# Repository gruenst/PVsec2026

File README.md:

# Open Source Hardware for Mobile String Power Acquisition of Solar Parks
Circuitpython and C++ based measurement system for Photovoltaic Installations. Up to 10 current clamps can be integrated, additional voltage, current and module temperature acquisition.

## Purpose
 * Open-source enhancements of publicly available hardware resources with LoRa radio for long range sensor data acquisition capability (no mesh network).
 * Complete system for measuring solar parks with flawed or without string monitoring
 * Versatile alternative to IV curve acquisition systems specifically for systems without single string accessibility - adapt to your own liking.

## Usage
 * Plug device in, opens up as USB stick (circuitpython)
 * Open .html file in Web Serial API compatible browser (Chrome, Edge, Opera; see https://developer.mozilla.org/en-US/docs/Web/API/Serial)
 * Use browser as GUI, connect to device and send/receive commands to/from device via serial interface
 * commands will be forwarded via LoRa RFM98W radio chip to remote device
 
## Content
 - Descriptions:    Short descriptions of each system with pictures 
 - PCBs, BOM:       EAGLE Cad PCB files, list of components
 - Housing:         3D STP files for 3D printing
 - Circuit Python:  Circuitpython .uf2, device code
 - GUI:             code.py for device, .html code with .js elements for GUI control, Arduino C++ code, web Serial or WLAN websocket control
 - bootloader:      Atmel SAMD bootloader for JLink
[https://learn.adafruit.com/how-to-program-samd-bootloaders](https://learn.adafruit.com/how-to-program-samd-bootloaders)

## Manual
 - Make PCB, solder components
 - flash bootloader using .bin file, e.g. via JLink, see https://learn.adafruit.com/how-to-program-samd-bootloaders
 - mount device via usb, put into bootloader mode, upload circuitpython .uf2 file
 - copy circuitpython8 lib elements to /lib directory on device
 - put code.py to device
 - upload .html file to device, adjust accordingly
 enjoy!
 
[Grn.Solar](https://www.grn.solar)
 
 Big shoutouts to [Adafruit](https://www.adafruit.com "Adafruit rocks") and Flaticon.

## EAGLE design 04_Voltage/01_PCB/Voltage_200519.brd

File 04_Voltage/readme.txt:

Lazy build for embedding a Phoenix Contact DC voltage level shifter (SCK-M-U-1500V) into a 3D printed case.
These components should be on the board:
 - 24V supply for the Phoenix Contact, power by 5V:  Murata NME0524DC
 - Adafruit ADS1115 breakout board
 - Adafruit PowerBoost 1000 Charger
 - Adafruit ItsyBitys M4 express
 
Embedding everything on a single PCB would be beneficial, but using an industry standard for 1500V string voltages seems reasonable.

DC connection via panel mount plugs (banana or solar connectors).
Power switch, with LED.
USB and SMA antenna plugs recommended.

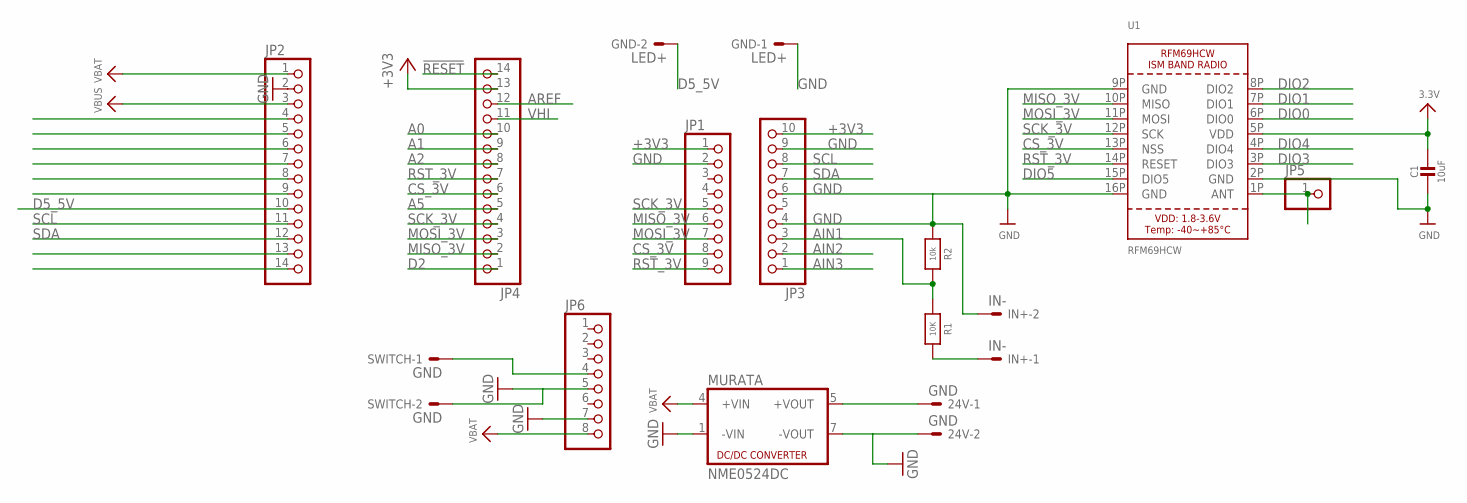
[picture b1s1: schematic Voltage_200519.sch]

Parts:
24V: GND; 332-02
C1: 10uF; 0805-NO@1
GND: LED+; 332-02
IN+: IN-; 332-02
JP1: HEADER-1X970MIL; 1X09_ROUND_70
JP2, JP4: HEADER-1X14; 1X14_ROUND70
JP3: HEADER-1X1070MIL; 1X10_ROUND70
JP5: HEADER-1X1ROUND; 1X01_ROUND
JP6: HEADER-1X8ROUND; 1X08_ROUND
MURATA: NME0524DC; 8DIL-4
R1: 10K; 0805-NO
R2: 10k; 0805-NO
SWITCH: GND; 332-02
U1: RFM69HCW; RFMHCW_SMT

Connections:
!RESET: JP4.14
+3V3: C1.1, JP1.1, JP3.10, JP4.13, U1.5P (VDD)
A0: JP4.10
A1: JP4.9
A2: JP4.8
A5: JP4.5
AIN1: JP3.3, R1.1, R2.2
AIN2: JP3.2
AIN3: JP3.1
AREF: JP4.12
CS_3V: JP1.8, JP4.6, U1.13P (NSS)
D2: JP4.1
D5_5V: GND.2, JP2.10
D7: JP2.9
D9: JP2.8
D10: JP2.7
D11: JP2.6
D12: JP2.5
D13: JP2.4
DIO0: U1.6P (DIO0)
DIO1: U1.7P (DIO1)
DIO2: U1.8P (DIO2)
DIO3: U1.3P (DIO3)
DIO4: U1.4P (DIO4)
DIO5: U1.15P (DIO5)
GND: 24V.2, C1.2, GND.1, IN+.2, JP1.2, JP2.2, JP3.4, JP3.6, JP3.9, JP6.5, JP6.7, MURATA.1 (-VIN), MURATA.7 (-VOUT), R2.1, SWITCH.2, U1.2P (GND), U1.9P (GND), U1.16P (GND)
MISO_3V: JP1.6, JP4.2, U1.10P (MISO)
MOSI_3V: JP1.7, JP4.3, U1.11P (MOSI)
unnamed: JP5.1, U1.1P (ANT)
unnamed: JP6.4, SWITCH.1
unnamed: IN+.1, R1.2
unnamed: 24V.1, MURATA.5 (+VOUT)
RST_3V: JP1.9, JP4.7, U1.14P (RESET)
RX_D0: JP2.14
SCK_3V: JP1.5, JP4.4, U1.12P (SCK)
SCL: JP2.11, JP3.8
SDA: JP2.12, JP3.7
TX_D1: JP2.13
VBAT: JP2.1, JP6.8, MURATA.4 (+VIN)
VBUS: JP2.3
VHI: JP4.11

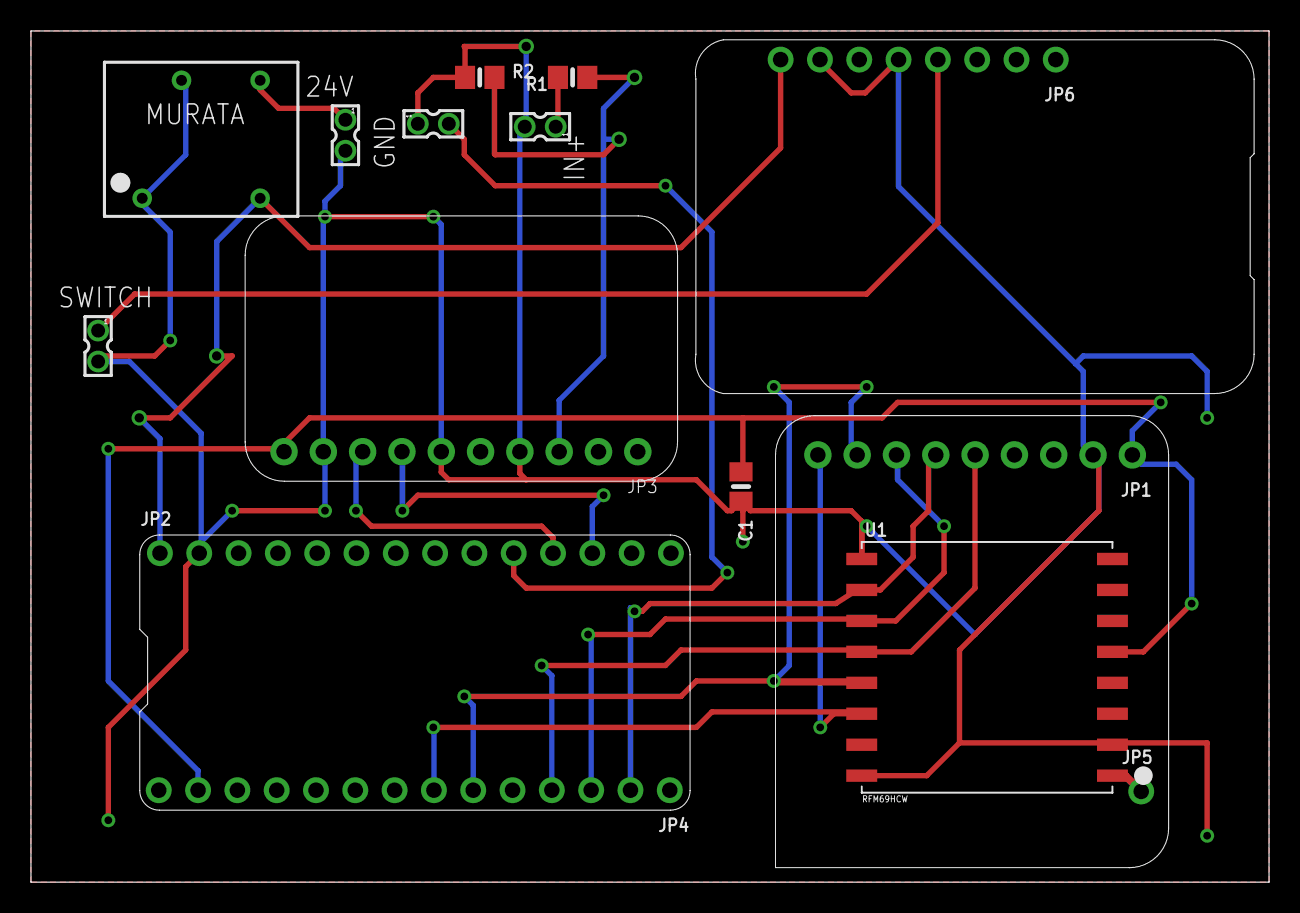
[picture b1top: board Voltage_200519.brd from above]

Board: 2 copper layers, 80.0 x 55.0 mm, 15 parts (0 on the bottom side), 16 nets.

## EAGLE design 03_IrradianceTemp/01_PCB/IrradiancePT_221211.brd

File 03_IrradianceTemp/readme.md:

# irradiance sensor with module temperature acquisition

Modification/hack of standard M&T irradiance sensors with an own-made PCB, and battery for independent operation.
As the current clamps, this is base don the Adafruit Itsybitsy M4 Express, so the code can be adapted/changed in the field with any computer (mounts as USB stick).
There is an USB B and C adapter for charging and programming.
There are soldering ports for adding a power switch, and adding an indicator LED. Alternatively, use a LED button.
PT temperature acquisition is done with a simple resistor bridge, as usually attachment of field sensors are by far the higher source of uncertainty than wire resistances.
But feel free to add a proper 4wire PT reading circuit (e.g. MAX31865), which was tested in yet another implementation.
As PT sensors, I recommend foil based ones with temperature conductive pastes. But whichever sensor, there is a lot to learn using them.

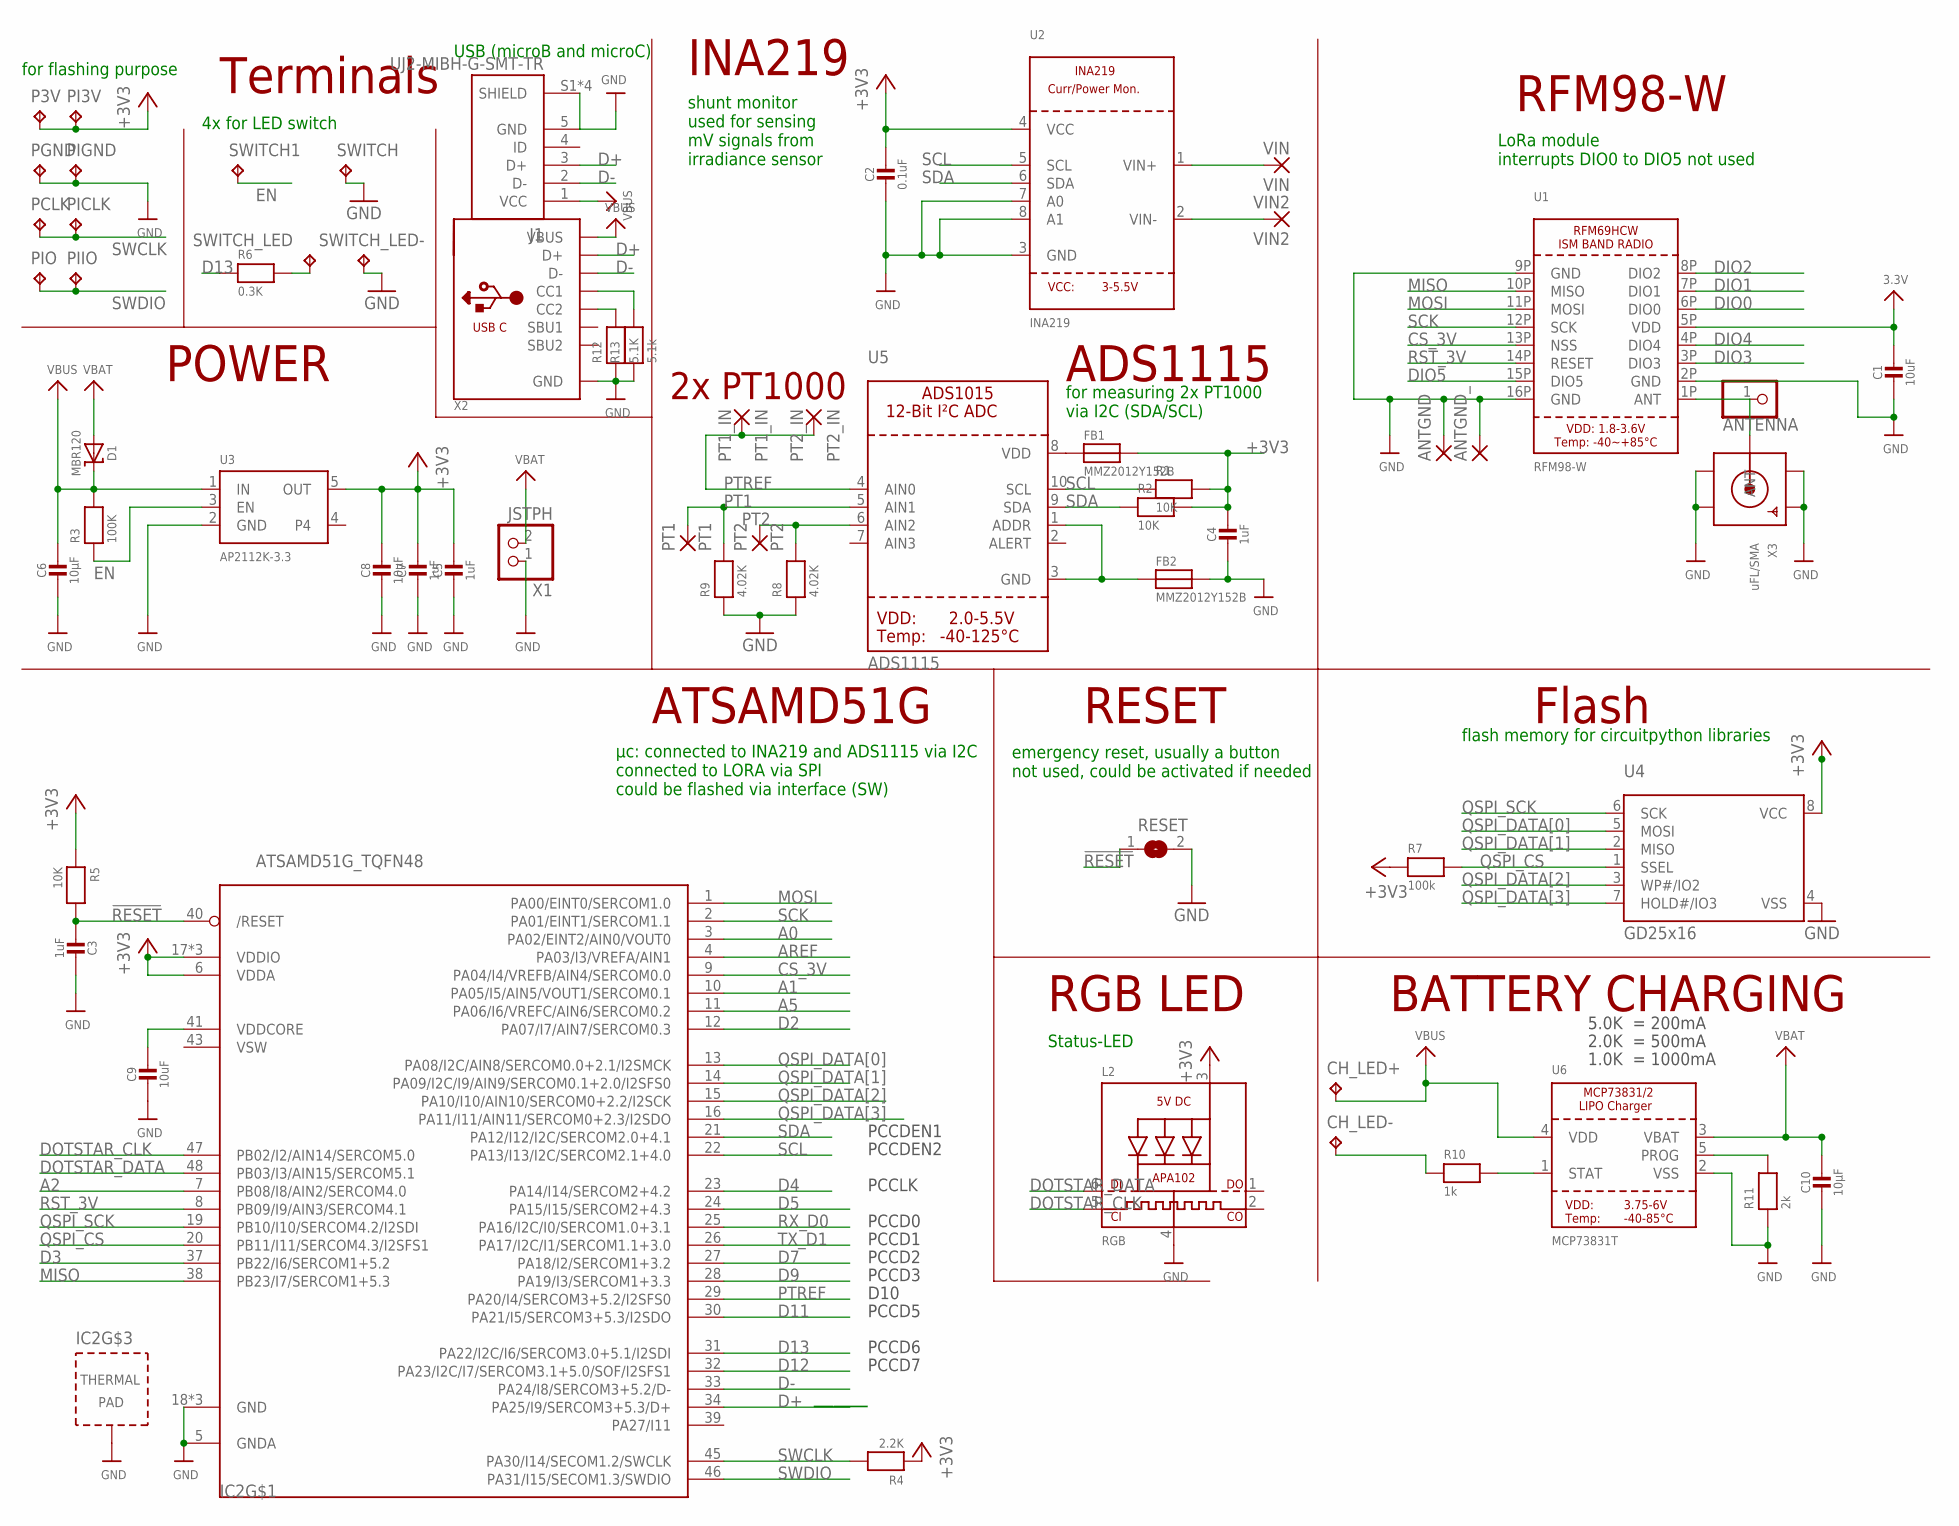
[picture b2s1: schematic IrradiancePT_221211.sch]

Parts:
ANTENNA: HEADER-1X1ROUND; 1X01_ROUND
ANTGND: SMD5; SMD2,54-5,08
ANTGND_: SMD5; SMD2,54-5,08
C1: 10uF; 0805-NO
C2: 0.1uF; 0603-NO
C3: 1uF; _0603MP
C4, C5, C7: 1uF; 0603-NO
C6, C8, C10: 10µF; 0805-NO
C9: 10uF; _0805MP
CH_LED+: TPPAD1-13; P1-13
CH_LED-: TPPAD1-13; P1-13
D1: MBR120; SOD-123
FB1, FB2: MMZ2012Y152B; 0805
IC2: ATSAMD51G_TQFN48; TQFN48_7MM
J1: UJ2-MIBH-G-SMT-TR; CUI_UJ2-MIBH-G-SMT-TR
L2: RGB; APA102_2020
P3V: TPTP20R; TP20R
PCLK: TPTP20R; TP20R
PGND: TPTP20R; TP20R
PI3V: TPPAD1-13; P1-13
PICLK: TPPAD1-13; P1-13
PIGND: TPPAD1-13; P1-13
PIIO: TPPAD1-13; P1-13
PIO: TP20R
PT1: PT1; 1,6/0,9
PT1_IN: PT1_IN; 1,6/0,9
PT2: PT2; 1,6/0,9
PT2_IN: PT2_IN; 1,6/0,9
R1, R2, R5: 10K; 0805
R3: 100K; 0805
R4: 2.2K; 0805
R6: 0.3K; 0805
R7: 100k; 0805
R8, R9: 4.02K; 0805
R10: 1k; 0805
R11: 2k; 0805
R12: 5.1K; 0805
R13: 5.1k; 0805
RESET: SOLDERJUMPER; SOLDERJUMPER_ARROW_NOPASTE
SWITCH, SWITCH1: TPPAD1-13; P1-13
SWITCH_LED: TPPAD1-13; P1-13
SWITCH_LED-: TPPAD1-13; P1-13
U1: RFM98-W; RFMHCW_SMT
U2: INA219; SOT23-8
U3: AP2112K-3.3; SOT23-5
U4: GD25x16; USON8
U5: ADS1115; MSOP10
U6: MCP73831T; SOT23-5
VIN: VIN; 1,6/0,9
VIN2: VIN2; 1,6/0,9
X1: JSTPH; JSTPH2
X2: USB_C; USB_C_CUSB31-CFM2AX-01-X
X3: uFL/SMA; SMA_EDGELAUNCH_UFL

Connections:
!RESET: C3.2, IC2.40 (/RESET), R5.2, RESET.1
+3V3: C1.1, C2.1, C4.1, C5.1, C7.1, C8.1, FB1.2, IC2.6 (VDDA), IC2.17 (VDDIO), IC2.36 (VDDIO), IC2.44 (VDDIO), L2.3 (VDD), P3V.TP, PI3V.TP, R1.2, R2.2, R4.1, R5.1, R7.1, U1.5P (VDD), U2.4 (VCC), U3.5 (OUT), U4.8 (VCC)
A0: IC2.3 (PA02/EINT2/AIN0/VOUT0)
A1: IC2.10 (PA05/I5/AIN5/VOUT1/SERCOM0.1)
A2: IC2.7 (PB08/I8/AIN2/SERCOM4.0)
A5: IC2.11 (PA06/I6/VREFC/AIN6/SERCOM0.2)
AREF: IC2.4 (PA03/I3/VREFA/AIN1)
CS_3V: IC2.9 (PA04/I4/VREFB/AIN4/SERCOM0.0), U1.13P (NSS)
D2: IC2.12 (PA07/I7/AIN7/SERCOM0.3)
D3: IC2.37 (PB22/I6/SERCOM1+5.2)
D4: IC2.23 (PA14/I14/SERCOM2+4.2)
D5: IC2.24 (PA15/I15/SERCOM2+4.3)
D7: IC2.27 (PA18/I2/SERCOM1+3.2)
D9: IC2.28 (PA19/I3/SERCOM1+3.3)
D11: IC2.30 (PA21/I5/SERCOM3+5.3/I2SDO)
D12: IC2.32 (PA23/I2C/I7/SERCOM3.1+5.0/SOF/I2SFS1)
D13: IC2.31 (PA22/I2C/I6/SERCOM3.0+5.1/I2SDI), R6.1
D+: IC2.34 (PA25/I9/SERCOM3+5.3/D+), J1.3 (D+), X2.A6 (D+), X2.B6 (D+)
D-: IC2.33 (PA24/I8/SERCOM3+5.2/D-), J1.2 (D-), X2.A7 (D-), X2.B7 (D-)
DIO0: U1.6P (DIO0)
DIO1: U1.7P (DIO1)
DIO2: U1.8P (DIO2)
DIO3: U1.3P (DIO3)
DIO4: U1.4P (DIO4)
DIO5: U1.15P (DIO5)
DOTSTAR_CLK: IC2.47 (PB02/I2/AIN14/SERCOM5.0), L2.5 (CKI)
DOTSTAR_DATA: IC2.48 (PB03/I3/AIN15/SERCOM5.1), L2.6 (DI)
EN: R3.1, SWITCH1.TP, U3.3 (EN)
GND: ANTGND.1, ANTGND_.1, C1.2, C2.2, C3.1, C4.2, C5.2, C6.2, C7.2, C8.2, C9.2, C10.2, FB2.2, IC2.5 (GNDA), IC2.18 (GND), IC2.35 (GND), IC2.42 (GND), IC2.THERMAL (TP), J1.5 (GND), J1.S1 (SHIELD), J1.S2 (SHIELD), J1.S3 (SHIELD), J1.S4 (SHIELD), L2.4 (GND), PGND.TP, PIGND.TP, R8.1, R9.1, R11.1, R12.1, R13.1, RESET.2, SWITCH.TP, SWITCH_LED-.TP, U1.2P (GND), U1.9P (GND), U1.16P (GND), U2.3 (GND), U2.7 (A0), U2.8 (A1), U3.2 (GND), U4.4 (VSS), U6.2 (VSS), X1.1, X2.A1B12 (GND), X2.B1A12 (GND), X3.GND@1 (GND1), X3.GND@2 (GND2), X3.GND@3 (GND3), X3.GND@4 (GND4)
GND_IN: FB2.1, U5.1 (ADDR), U5.3 (GND)
MISO: IC2.38 (PB23/I7/SERCOM1+5.3), U1.10P (MISO)
MOSI: IC2.1 (PA00/EINT0/SERCOM1.0), U1.11P (MOSI)
unnamed: ANTENNA.1, U1.1P (ANT), X3.P (ANT)
unnamed: R6.2, SWITCH_LED.TP
unnamed: U2.1 (VIN+), VIN.1
unnamed: U2.2 (VIN-), VIN2.1
unnamed: FB1.1, U5.8 (VDD)
unnamed: CH_LED-.TP, R10.1
unnamed: R10.2, U6.1 (STAT)
unnamed: R11.2, U6.5 (PROG)
unnamed: R13.2, X2.A5 (CC1)
unnamed: R12.2, X2.B5 (CC2)
PT1: PT1.1, R9.2, U5.5 (AIN1)
PT2: PT2.1, R8.2, U5.6 (AIN2)
PTREF: IC2.29 (PA20/I4/SERCOM3+5.2/I2SFS0), PT1_IN.1, PT2_IN.1, U5.4 (AIN0)
QSPI_CS: IC2.20 (PB11/I11/SERCOM4.3/I2SFS1), R7.2, U4.1 (SSEL)
QSPI_DATA[0]: IC2.13 (PA08/I2C/AIN8/SERCOM0.0+2.1/I2SMCK), U4.5 (MOSI)
QSPI_DATA[1]: IC2.14 (PA09/I2C/I9/AIN9/SERCOM0.1+2.0/I2SFS0), U4.2 (MISO)
QSPI_DATA[2]: IC2.15 (PA10/I10/AIN10/SERCOM0+2.2/I2SCK), U4.3 (WP#/IO2)
QSPI_DATA[3]: IC2.16 (PA11/I11/AIN11/SERCOM0+2.3/I2SDO), U4.7 (HOLD#/IO3)
QSPI_SCK: IC2.19 (PB10/I10/SERCOM4.2/I2SDI), U4.6 (SCK)
RST_3V: IC2.8 (PB09/I9/AIN3/SERCOM4.1), U1.14P (RESET)
RX_D0: IC2.25 (PA16/I2C/I0/SERCOM1.0+3.1)
SCK: IC2.2 (PA01/EINT1/SERCOM1.1), U1.12P (SCK)
SCL: IC2.22 (PA13/I13/I2C/SERCOM2.1+4.0), R1.1, U2.5 (SCL), U5.10 (SCL)
SDA: IC2.21 (PA12/I12/I2C/SERCOM2.0+4.1), R2.1, U2.6 (SDA), U5.9 (SDA)
SWCLK: IC2.45 (PA30/I14/SECOM1.2/SWCLK), PCLK.TP, PICLK.TP, R4.2
SWDIO: IC2.46 (PA31/I15/SECOM1.3/SWDIO), PIIO.TP, PIO.TP
TX_D1: IC2.26 (PA17/I2C/I1/SERCOM1.1+3.0)
VBAT: C10.1, D1.A, U6.3 (VBAT), X1.2
VBUS: C6.1, CH_LED+.TP, D1.C, J1.1 (VCC), R3.2, U3.1 (IN), U6.4 (VDD), X2.A4B9 (VBUS), X2.B4A9 (VBUS)
VDDCORE: C9.1, IC2.41 (VDDCORE)
VSW: IC2.43 (VSW)

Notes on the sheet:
Terminals
RFM98-W
INA219
POWER
RESET
µc: connected to INA219 and ADS1115 via I2C connected to LORA via SPI could be flashed via interface (SW)
PCCDEN1
PCCDEN2
PCCD0
PCCD1
PCCD2
PCCD3
D10
PCCD5
PCCD6
PCCD7
PCCLK
Flash
RGB LED
ATSAMD51G
LoRa module interrupts DIO0 to DIO5 not used
shunt monitor used for sensing mV signals from irradiance sensor
emergency reset, usually a button not used, could be activated if needed
flash memory for circuitpython libraries
ADS1115
2x PT1000
Status-LED
for flashing purpose
USB (microB and microC)
for measuring 2x PT1000 via I2C (SDA/SCL)
5.0K = 200mA
2.0K = 500mA
1.0K = 1000mA
BATTERY CHARGING
4x for LED switch

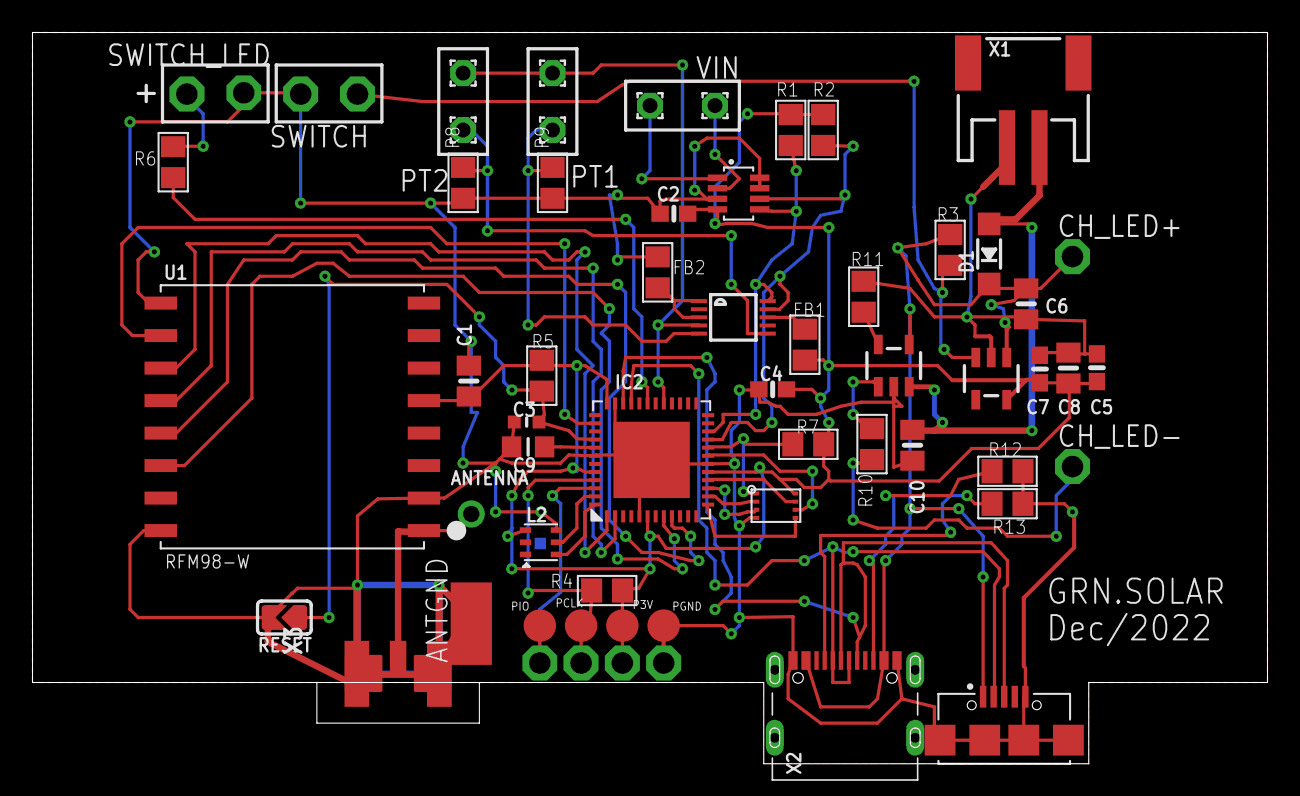
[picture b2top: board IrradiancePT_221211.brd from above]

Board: 2 copper layers, 76.0 x 45.0 mm, 62 parts (1 on the bottom side), 41 nets.

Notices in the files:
parts and their libraries:
microbuilder: This work is placed in the public domain, and may be freely used for commercial and non-commercial work with the following conditions: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
